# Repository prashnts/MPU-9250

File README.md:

# Human Activing Recognition

## What is it?

This is my school project from 2015 on using accelerometer data for human activity recognition task.

> School Project done at CIC, University of Delhi.
> I will add all the notes/pages/etc I have soon before archiving it.
> Note that this paper was never submitted anywhere, but I plan to put it on arxiv.

## What's in here?

In the repo, there is:

- MPU–9250 fw, in few flavours, eg. SD card data logging.
- Schematics of the arduino data logger
- Python code for training a SVM classifier
- Some pre-built models to classify the accelerometer data
- Raw dataset i created with motion data
- Project report Submitted in school
- Pretty graphs and illustrations
- An iphone app (in xcode!) for streaming accelerometer data over wifi in udp packets
- A python server which takes the streaming data and shows classified predictions in console
- A data logger script to put the streaming data into InfluxDB time series
- Raw dataset obtained from two universities And some 3D point cloud visualisation

Based heavily on MPU-9250 example code by [kriswiner/MPU-9250](https://github.com/kriswiner/MPU-9250).

## Licenses

- **Code License**: MIT
- **Dataset License**: CC0, Public Domain
- **Illustrations License**: CC-BY-SA-NC
- **Report License**: Property of Delhi University
- **Report source License**: CC0
- **Trained Model License**: WTFPL

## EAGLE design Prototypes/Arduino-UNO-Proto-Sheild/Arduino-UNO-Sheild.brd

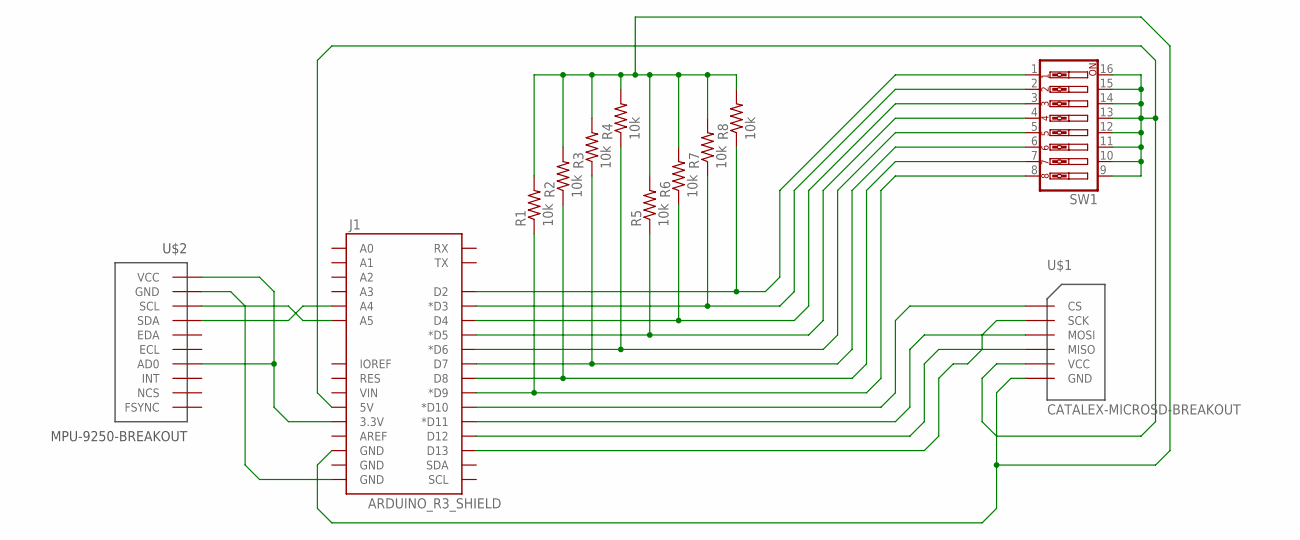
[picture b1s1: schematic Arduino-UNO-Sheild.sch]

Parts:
J1: ARDUINO_R3_SHIELD; UNO_R3_SHIELD
R1, R2, R3, R4, R5, R6, R7, R8: 10k; AXIAL-0.3-KIT
SW1: SW_DIP-8; DIPSWITCH-08
U$1: CATALEX-MICROSD-BREAKOUT
U$2: MPU-9250-BREAKOUT

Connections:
unnamed: J1.A4, U$2.SDA
unnamed: J1.A5, U$2.SCL
unnamed: J1.3.3V, U$2.AD0, U$2.VCC
unnamed: J1.GND@0 (GND), U$2.GND
unnamed: J1.D10 (*D10), U$1.CS
unnamed: J1.D13, U$1.SCK
unnamed: J1.D11 (*D11), U$1.MOSI
unnamed: J1.D12, U$1.MISO
unnamed: J1.D9 (*D9), R1.P$1 (1), SW1.8
unnamed: J1.D8, R2.P$1 (1), SW1.7
unnamed: J1.D7, R3.P$1 (1), SW1.6
unnamed: J1.D6 (*D6), R4.P$1 (1), SW1.5
unnamed: J1.D5 (*D5), R5.P$1 (1), SW1.4
unnamed: J1.D4, R6.P$1 (1), SW1.3
unnamed: J1.D3 (*D3), R7.P$1 (1), SW1.2
unnamed: J1.D2, R8.P$1 (1), SW1.1
unnamed: J1.5V, SW1.9, SW1.10, SW1.11, SW1.12, SW1.13, SW1.14, SW1.15, SW1.16, U$1.VCC
unnamed: J1.GND@2 (GND), R1.P$2 (2), R2.P$2 (2), R3.P$2 (2), R4.P$2 (2), R5.P$2 (2), R6.P$2 (2), R7.P$2 (2), R8.P$2 (2), U$1.GND

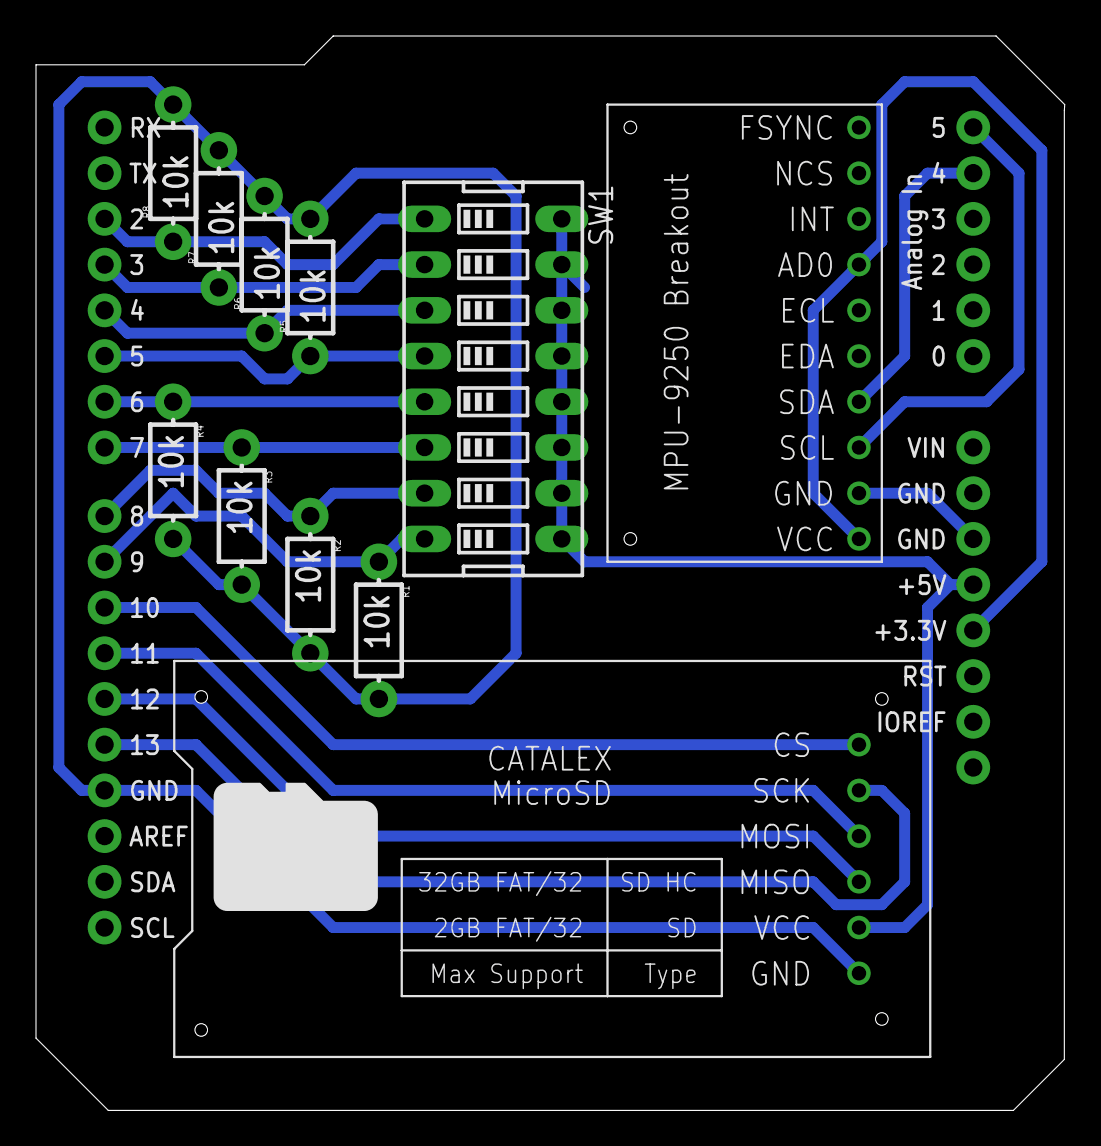
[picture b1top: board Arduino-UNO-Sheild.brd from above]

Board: 2 copper layers, 57.1 x 59.7 mm, 12 parts (0 on the bottom side), 18 nets.

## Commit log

2015-07-28 Added 'AvrCopter' firmware for modification
2015-07-28 Added the raw register map, from MPU-9250RegisterMap datasheet. Unformatted, or coded, hence requires further regex parsing to convert into a C header code.
2015-07-28 Added the magnetometer register values
2015-07-28 Fixed the register map and matched it to the C syntax
2015-07-28 Fixed the register map and matched it to the C syntax and added proper syntax tabs
2015-07-29 Firmware
2015-07-29 Still works. :P
2015-07-29 Added the Filter algorithm file
2015-07-29 Fixed the shitty indentation in the filter script.
2015-07-29 Added more changes to the original code and added the Readme file
2015-07-29 Fixed up more syntax, moved the aux/necessary functions to the Library file.
2015-07-29 Finished up the Wire abstraction library.
2015-07-29 Fixed the indentation of the MadgwickQuaternionUpdate method
2015-07-29 Multiple syntatical fixes
2015-07-30 Fixed up one method
2015-07-30 Fixes
2015-07-30 Removal
2015-08-01 Serialization, working
2015-08-05 Removed useless project files
2015-08-05 Added the Data Logger
2015-08-05 Many changes
2015-08-08 Sheild - Fixes
2015-08-08 Module libraries
2015-08-12 Added the Explosive codes.
2015-08-12 Finished up the Button Reads
2015-08-13 Fixes, Motion Logger
2015-08-13 More changes
2015-08-13 Finished up a preliminary Firmware.
2015-08-13 Fixed most of the Codes Here.
2015-08-13 Merged the register map.
2015-08-13 Added zero padding in file name.
2015-08-17 Added a test scaffold.
2015-08-19 Added the PC project
2015-08-19 Test data and the Three.JS library.
    Added the sensor datasets and began the library.
2015-08-19 Somewhat.
2015-08-19 Some.
2015-08-19 Point. Shit. :(
2015-08-21 Damn it .DS_Store!
2015-08-21 IMU data.
2015-08-29 Added some sample data.
2015-08-29 OMG So many changes.
2015-08-30 UDP beauty
2015-08-30 UDP Logger
2015-08-30 SVM!
2015-08-31 Pickled Data
2015-09-01 Added more data dump and began with the newer periodic properties.
2015-09-02 More test dumps
2015-09-02 A load of changes to the internal API to make life easier.
2015-09-05 Properly decorated library ❤️
2015-09-05 Renamed the class, and extended the functionality.
2015-09-05 More beauty.
2015-09-06 Reordered, more syntactic sugar.
2015-09-06 Multiple changes.
2015-09-06 Decommissioned.
2015-09-07 More
2015-09-08 Changes.
2015-09-09 Eigenvalues!
2015-09-09 Feature!
2015-09-09 Added visualisation scatterplot.
2015-09-09 Done.
2015-09-09 Loads.
2015-09-09 More trained samples.
2015-09-10 Partial Docs.
2015-09-14 Routines
2015-09-14 Tests
2015-09-14 PLOTS!
2015-09-15 Added Autocorrelation function method.
2015-09-15 AHRS visuals.
2015-09-15 Energy expts.
2015-09-15 Restored.
2015-09-16 Added presentation
2015-09-17 Multiple changes!
2015-09-17 Finished.
2015-09-18 Began the Annotations data training.
2015-09-21 Stupid Names.
2015-09-23 Added Import Tools.
2015-09-23 Moar!
2015-09-24 Multiple routines
2015-09-25 Annotations and Comments.
2015-09-25 Imports.
2015-09-25 Annotation Getters.
2015-09-25 Annotations.
2015-09-25 Time
2015-09-25 iPhone App.
2015-09-25 xcode.
2015-09-27 Test
2015-09-27 More!
2015-09-27 Fits.
2015-09-27 Help :(
2015-09-27 Line
2015-09-27 Distance
2015-09-28 Frechet Distance Refactors.
2015-09-28 Refactors.
2015-09-29 Helper Features
2015-09-29 This commit breaks multiple routines.
2015-09-29 Samples and Newer Methods.
2015-09-30 Polygons!
2015-10-01 Lambda Captures and Gradient Bins
2015-10-01 KP, GD.
2015-10-01 Stuff.
2015-10-03 Sliding Window
2015-10-03 Hmmm.
2015-10-05 Created the (hopefully) final set.
2015-10-05 Probes
2015-10-05 Import routine.
2015-10-06 features.
2015-10-06 Preliminary features.
2015-10-06 intermediary features
2015-10-06 Training routine
2015-10-07 SVM Train.
2015-10-07 Schemes.
2015-10-08 Yep, works!
2015-10-10 Ftrs
2015-10-10 Features. Final.
2015-10-11 Twente routine.
2015-10-11 Chained dataset.
2015-10-15 A few label changes.
2015-10-16 Addition of third dataset.
2015-10-21 Adds more label categories.
2015-10-26 More.
2015-10-27 Added the colormap, and routine consolidation.
2015-11-02 Final
2020-02-02 add school report i finally submitted
2020-02-03 Add more docs for this project, update readme.

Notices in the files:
parts and their libraries:
SparkFun-Boards: Licensing: Creative Commons ShareAlike 4.0 International - https://creativecommons.org/licenses/by-sa/4.0
